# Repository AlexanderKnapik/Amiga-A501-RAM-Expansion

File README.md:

# Amiga-A501-RAM-Expansion
RAM Expansion card for Amiga 500.

Project under construction. 

No warranty provided. Building and using this card is done so under your own risk.

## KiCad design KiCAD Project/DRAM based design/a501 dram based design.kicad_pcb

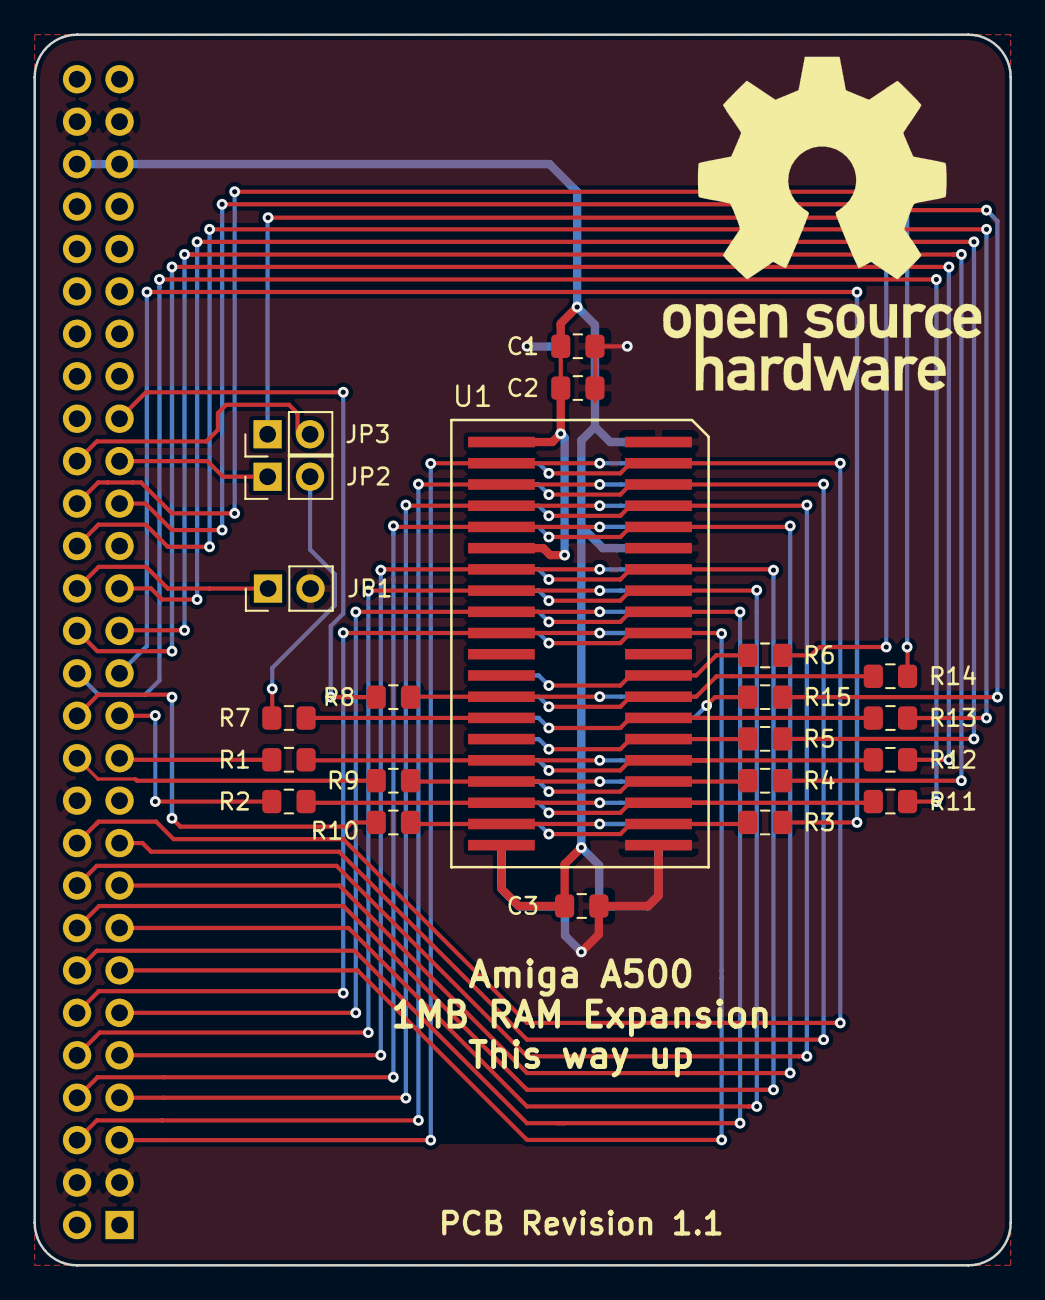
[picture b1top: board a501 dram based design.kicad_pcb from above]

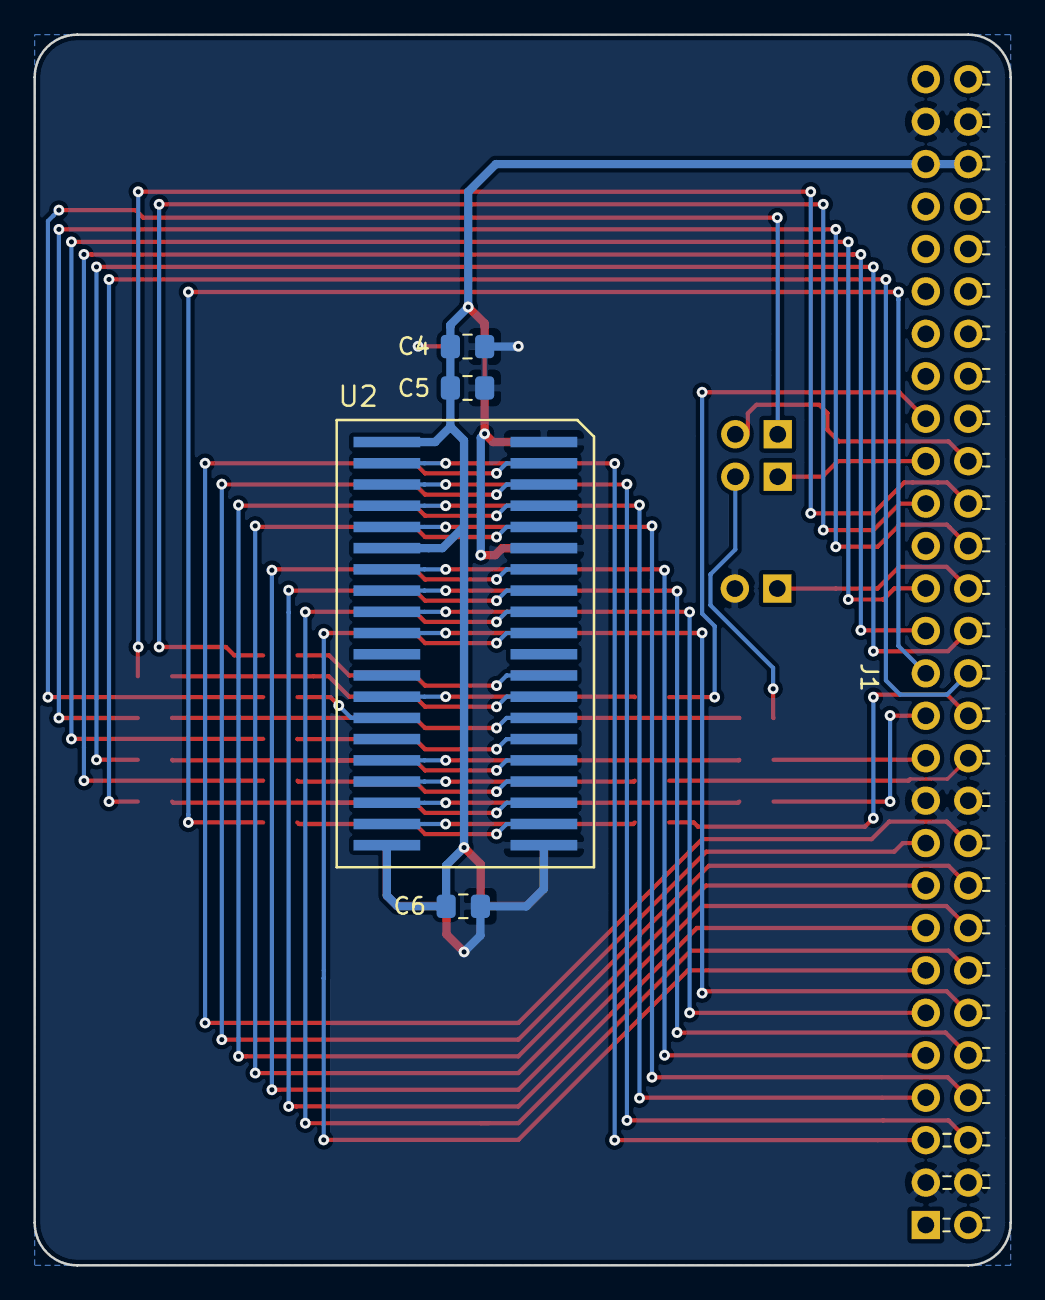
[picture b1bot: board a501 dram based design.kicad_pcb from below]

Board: 2 copper layers, 58.4 x 73.7 mm, 27 parts (5 on the bottom side), 51 nets.

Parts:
C1, C4: 10u; C_0805_2012Metric_Pad1.15x1.40mm_HandSolder
C2, C3, C5, C6: 10n; C_0805_2012Metric_Pad1.15x1.40mm_HandSolder
J1: Conn_02x28_Odd_Even; Pin_Header_Angled_Female_2x28_Pitch2.54mm
JP1, JP2, JP3: Jumper; Pin_Header_Straight_1x02_Pitch2.54mm
R1, R2, R3, R4, R5, R6, R7, R8, R9, R10, R11, R12, R13, R14, R15: 4K7; R_0805_2012Metric_Pad1.15x1.40mm_HandSolder
U1, U2: M11B416256A-35TG; SOJ-40

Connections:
+5V: C1.1, C2.1, C3.1, C4.1, C5.1, C6.1, J1.51, J1.52, U1.1, U1.6, U1.20, U2.1, U2.6, U2.20
/A0: R1.1, U1.16, U2.16
/A1: R9.2, U1.17, U2.17
/A2: R2.1, U1.18, U2.18
/A3: R10.2, U1.19, U2.19
/A4: R3.1, U1.22, U2.22
/A5: R11.2, U1.23, U2.23
/A6: R4.1, U1.24, U2.24
/A7: R12.2, U1.25, U2.25
/A8: R5.1, U1.26, U2.26
/DQ0: J1.5, U1.2, U2.2
/DQ1: J1.6, U1.3, U2.3
/DQ2: J1.7, U1.4, U2.4
/DQ3: J1.8, U1.5, U2.5
/DQ4: J1.9, U1.7, U2.7
/DQ5: J1.10, U1.8, U2.8
/DQ6: J1.11, U1.9, U2.9
/DQ7: J1.12, U1.10, U2.10
/DQ8: J1.13, U1.31, U2.31
/DQ9: J1.14, U1.32, U2.32
/DQ10: J1.15, U1.33, U2.33
/DQ11: J1.16, U1.34, U2.34
/DQ12: J1.17, U1.36, U2.36
/DQ13: J1.18, U1.37, U2.37
/DQ14: J1.19, U1.38, U2.38
/DQ15: J1.20, U1.39, U2.39
/~CASL: R6.1, U1.29, U2.29
/~CASU: R14.2, U1.28, U2.28
/~EXTICK: J1.32, JP1.1
/~OE: R13.2, U1.27, U2.27
/~RAS0: J1.37, JP2.1
/~RAS0out: R7.2, U1.14
/~RAS1: J1.38, JP3.2
/~RAS1out: R15.2, U2.14
/~WE: R8.1, U1.13, U2.13
GND: C1.2, C2.2, C3.2, C4.2, C5.2, C6.2, J1.3, J1.4, J1.21, J1.22, J1.53, J1.54, JP1.2, U1.21, U1.35, U1.40, U2.21, U2.35, U2.40
unnamed: J1.23, R1.2
unnamed: J1.24, R9.1
unnamed: J1.25, R2.2
unnamed: J1.26, R10.1
unnamed: J1.27, R3.2
unnamed: J1.28, R11.1
unnamed: J1.29, R4.2
unnamed: J1.30, R12.1
unnamed: J1.31, R5.2
unnamed: J1.34, R13.1
unnamed: J1.35, R6.2
unnamed: J1.36, R14.1
unnamed: J1.39, R8.2
unnamed: JP2.2, R7.1
unnamed: JP3.1, R15.1

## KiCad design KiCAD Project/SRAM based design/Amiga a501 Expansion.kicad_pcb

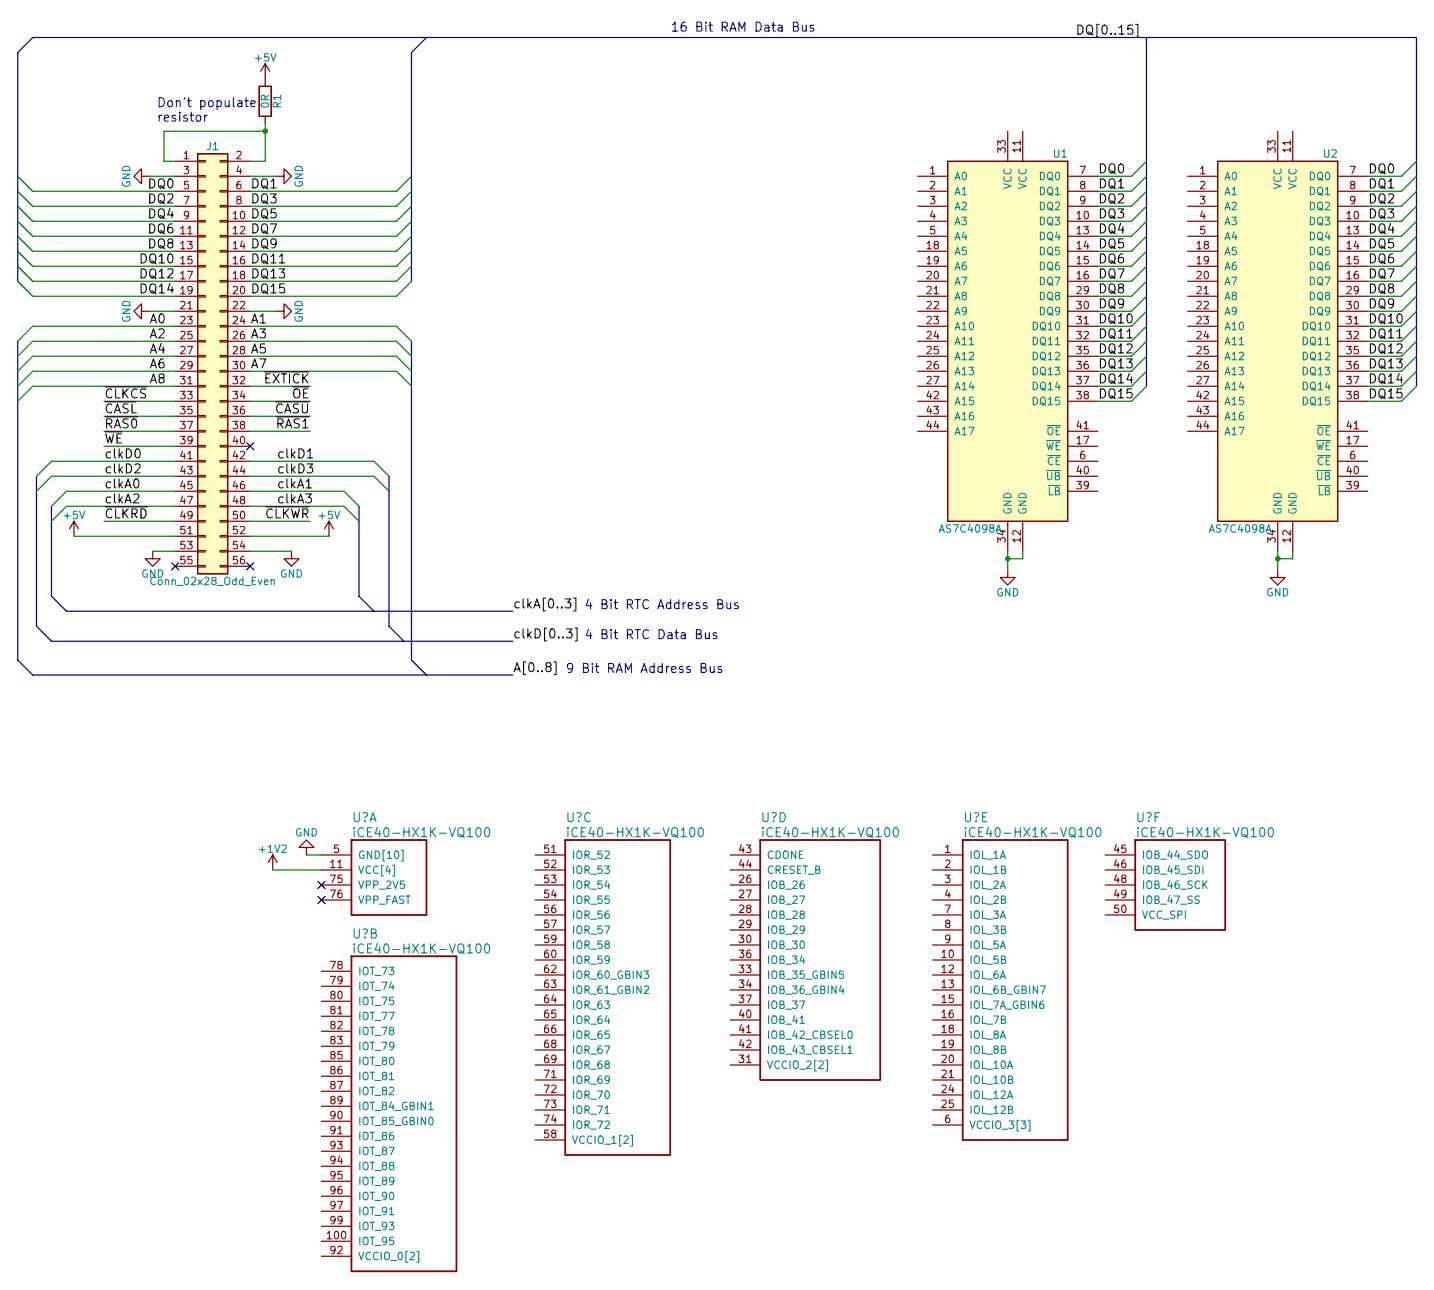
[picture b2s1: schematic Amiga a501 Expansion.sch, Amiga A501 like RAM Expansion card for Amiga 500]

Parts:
J1: Conn_02x28_Odd_Even; Pin_Header_Angled_2x28_Pitch2.54mm
R1: 0R; R_0805_HandSoldering
U1, U2: AS7C4098A; TSOP-44

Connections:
+5V: J1.51, J1.52, R1.1
/DQ0: J1.5, U1.7 (DQ0), U2.7 (DQ0)
/DQ1: J1.6, U1.8 (DQ1), U2.8 (DQ1)
/DQ2: J1.7, U1.9 (DQ2), U2.9 (DQ2)
/DQ3: J1.8, U1.10 (DQ3), U2.10 (DQ3)
/DQ4: J1.9, U1.13 (DQ4), U2.13 (DQ4)
/DQ5: J1.10, U1.14 (DQ5), U2.14 (DQ5)
/DQ6: J1.11, U1.15 (DQ6), U2.15 (DQ6)
/DQ7: J1.12, U1.16 (DQ7), U2.16 (DQ7)
/DQ8: J1.13, U1.29 (DQ8), U2.29 (DQ8)
/DQ9: J1.14, U1.30 (DQ9), U2.30 (DQ9)
/DQ10: J1.15, U1.31 (DQ10), U2.31 (DQ10)
/DQ11: J1.16, U1.32 (DQ11), U2.32 (DQ11)
/DQ12: J1.17, U1.35 (DQ12), U2.35 (DQ12)
/DQ13: J1.18, U1.36 (DQ13), U2.36 (DQ13)
/DQ14: J1.19, U1.37 (DQ14), U2.37 (DQ14)
/DQ15: J1.20, U1.38 (DQ15), U2.38 (DQ15)
unnamed: J1.1, J1.2, R1.2

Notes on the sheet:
Don't populate resistor
16 Bit RAM Data Bus
9 Bit RAM Address Bus
4 Bit RTC Data Bus
4 Bit RTC Address Bus

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
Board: 2 copper layers, 4 parts (0 on the bottom side), 19 nets, no tracks yet.

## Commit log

2018-03-29 Added RAM Datasheet
2018-03-29 Blank KiCAD Project
2018-06-10 Work on connecting data lines to the expansion header. TSOP-44 Footprint
2018-06-22 Work on verilog files. Started ram controller, made a flip flop array. Learning verilator synthesis now
2018-06-24 Started work on a DRAM based design instead to keep it simple
2018-06-27 Completed DRAM expansion design
2019-05-23 Adding the completed keypad prototype kicad files. Finished a long time ago, just forgot to push

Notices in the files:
KiCAD Project/Amiga a501 Expansion.sch:
Copyright (C) 2018 under the GNU General Public License v3.0 or any later version
KiCAD Project/DRAM based design/a501 dram based design.kicad_pcb:
Copyright (C) 2018 under the GNU GPL v3.0 or any later version
